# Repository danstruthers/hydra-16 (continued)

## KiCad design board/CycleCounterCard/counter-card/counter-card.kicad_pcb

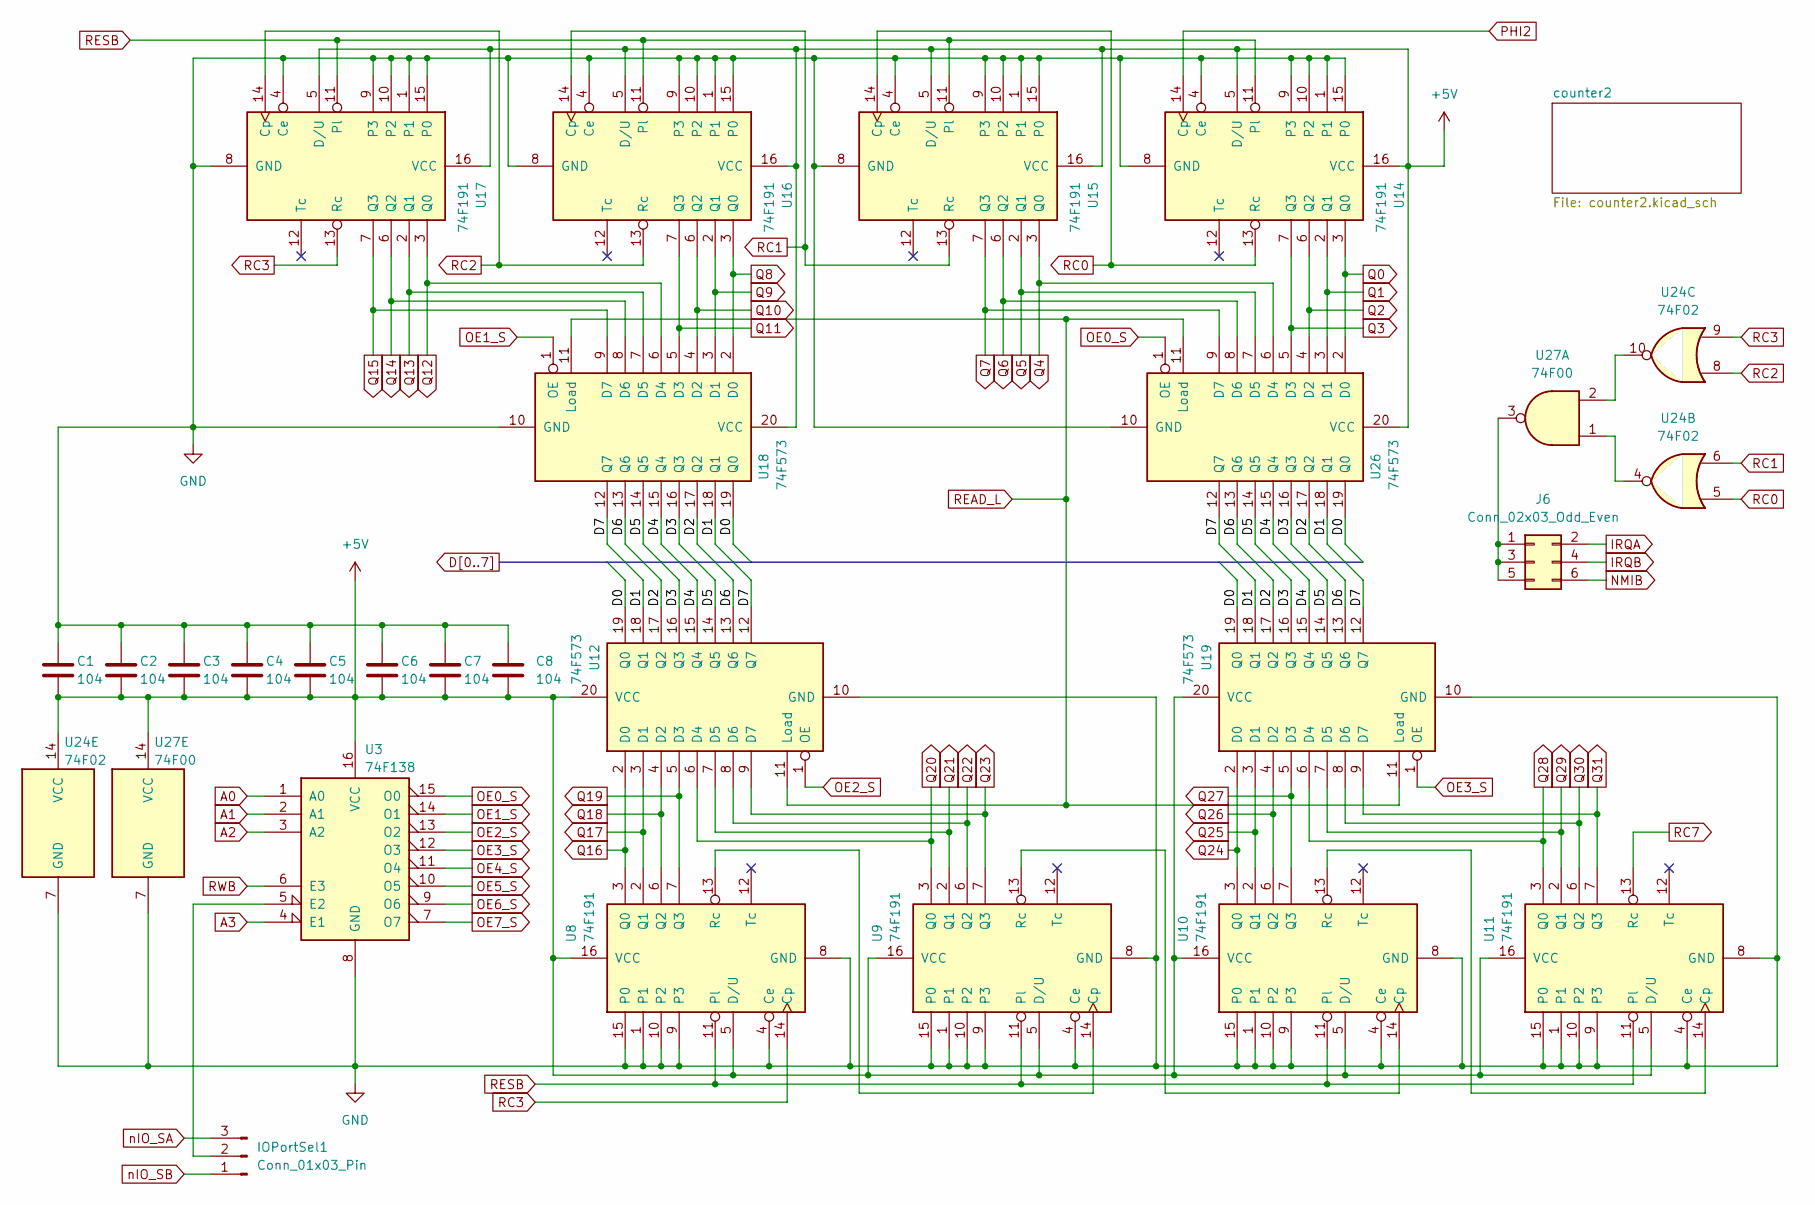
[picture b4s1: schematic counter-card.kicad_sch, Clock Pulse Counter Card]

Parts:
C1, C2, C3, C4, C5, C6, C7, C8: 104; C_Disc_D5.0mm_W2.5mm_P5.00mm
IOPortSel1: Conn_01x03_Pin; PinHeader_1x03_P2.54mm_Vertical
J6: Conn_02x03_Odd_Even; PinHeader_2x03_P2.54mm_Vertical
U3: 74F138; DIP-16_W7.62mm_Socket_LongPads
U8, U9, U10, U11, U14, U15, U16, U17: 74F191; DIP-16_W7.62mm_Socket_LongPads
U12, U18, U19, U26: 74F573; DIP-20_W7.62mm_Socket_LongPads
U24: 74F02; DIP-14_W7.62mm_Socket_LongPads
U27: 74F00; DIP-14_W7.62mm_Socket_LongPads

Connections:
+5V: C1.2, C2.2, C3.2, C4.2, C5.2, C6.2, C7.2, C8.2, U3.16 (VCC), U8.5 (D/U), U8.16 (VCC), U9.5 (D/U), U9.16 (VCC), U10.5 (D/U), U10.16 (VCC), U11.5 (D/U), U11.16 (VCC), U12.20 (VCC), U14.5 (D/U), U14.16 (VCC), U15.5 (D/U), U15.16 (VCC), U16.5 (D/U), U16.16 (VCC), U17.5 (D/U), U17.16 (VCC), U18.20 (VCC), U19.20 (VCC), U24.14 (VCC), U26.20 (VCC), U27.14 (VCC); also elsewhere on the board
A0: U3.1 (A0); also elsewhere on the board
A1: U3.2 (A1); also elsewhere on the board
A2: U3.3 (A2); also elsewhere on the board
A3: U3.4 (E1); also elsewhere on the board
D0: U12.19 (Q0), U18.19 (Q0), U19.19 (Q0), U26.19 (Q0); also elsewhere on the board
D1: U12.18 (Q1), U18.18 (Q1), U19.18 (Q1), U26.18 (Q1); also elsewhere on the board
D2: U12.17 (Q2), U18.17 (Q2), U19.17 (Q2), U26.17 (Q2); also elsewhere on the board
D3: U12.16 (Q3), U18.16 (Q3), U19.16 (Q3), U26.16 (Q3); also elsewhere on the board
D4: U12.15 (Q4), U18.15 (Q4), U19.15 (Q4), U26.15 (Q4); also elsewhere on the board
D5: U12.14 (Q5), U18.14 (Q5), U19.14 (Q5), U26.14 (Q5); also elsewhere on the board
D6: U12.13 (Q6), U18.13 (Q6), U19.13 (Q6), U26.13 (Q6); also elsewhere on the board
D7: U12.12 (Q7), U18.12 (Q7), U19.12 (Q7), U26.12 (Q7); also elsewhere on the board
GND: C1.1, C2.1, C3.1, C4.1, C5.1, C6.1, C7.1, C8.1, U3.8 (GND), U8.1, U8.4 (Ce), U8.8 (GND), U8.9 (P3), U8.10 (P2), U8.15 (P0), U9.1, U9.4 (Ce), U9.8 (GND), U9.9 (P3), U9.10 (P2), U9.15 (P0), U10.1, U10.4 (Ce), U10.8 (GND), U10.9 (P3), U10.10 (P2), U10.15 (P0), U11.1, U11.4 (Ce), U11.8 (GND), U11.9 (P3), U11.10 (P2), U11.15 (P0), U12.10 (GND), U14.1, U14.4 (Ce), U14.8 (GND), U14.9 (P3), U14.10 (P2), U14.15 (P0), U15.1, U15.4 (Ce), U15.8 (GND), U15.9 (P3), U15.10 (P2), U15.15 (P0), U16.1, U16.4 (Ce), U16.8 (GND), U16.9 (P3), U16.10 (P2), U16.15 (P0), U17.1, U17.4 (Ce), U17.8 (GND), U17.9 (P3), U17.10 (P2), U17.15 (P0), U18.10 (GND), U19.10 (GND), U24.7 (GND), U26.10 (GND), U27.7 (GND); also elsewhere on the board
IRQA: J6.2; also elsewhere on the board
IRQB: J6.4; also elsewhere on the board
NMIB: J6.6; also elsewhere on the board
unnamed: IOPortSel1.2, U3.5 (E2)
unnamed: J6.1, J6.3, J6.5, U27.3
unnamed: U8.13 (Rc), U9.14 (Cp)
unnamed: U9.13 (Rc), U10.14 (Cp)
unnamed: U10.13 (Rc), U11.14 (Cp)
unnamed: U24.4, U27.1
unnamed: U24.10, U27.2
OE0_S: U3.15 (O0), U26.1 (OE); also elsewhere on the board
OE1_S: U3.14 (O1), U18.1 (OE)
OE2_S: U3.13 (O2), U12.1 (OE)
OE3_S: U3.12 (O3), U19.1 (OE)
OE4_S: U3.11 (O4); also elsewhere on the board
OE5_S: U3.10 (O5); also elsewhere on the board
OE6_S: U3.9 (O6); also elsewhere on the board
OE7_S: U3.7 (O7); also elsewhere on the board
PHI2: U14.14 (Cp); also elsewhere on the board
Q0: U14.3 (Q0), U26.2 (D0); also elsewhere on the board
Q1: U14.2 (Q1), U26.3 (D1); also elsewhere on the board
Q2: U14.6 (Q2), U26.4 (D2); also elsewhere on the board
Q3: U14.7 (Q3), U26.5 (D3); also elsewhere on the board
Q4: U15.3 (Q0), U26.6 (D4); also elsewhere on the board
Q5: U15.2 (Q1), U26.7 (D5); also elsewhere on the board
Q6: U15.6 (Q2), U26.8 (D6); also elsewhere on the board
Q7: U15.7 (Q3), U26.9 (D7); also elsewhere on the board
Q8: U16.3 (Q0), U18.2 (D0); also elsewhere on the board
Q9: U16.2 (Q1), U18.3 (D1); also elsewhere on the board
Q10: U16.6 (Q2), U18.4 (D2); also elsewhere on the board
Q11: U16.7 (Q3), U18.5 (D3); also elsewhere on the board
Q12: U17.3 (Q0), U18.6 (D4); also elsewhere on the board
Q13: U17.2 (Q1), U18.7 (D5); also elsewhere on the board
Q14: U17.6 (Q2), U18.8 (D6); also elsewhere on the board
Q15: U17.7 (Q3), U18.9 (D7); also elsewhere on the board
Q16: U8.3 (Q0), U12.2 (D0); also elsewhere on the board
Q17: U8.2 (Q1), U12.3 (D1); also elsewhere on the board
Q18: U8.6 (Q2), U12.4 (D2); also elsewhere on the board
Q19: U8.7 (Q3), U12.5 (D3); also elsewhere on the board
Q20: U9.3 (Q0), U12.6 (D4); also elsewhere on the board
Q21: U9.2 (Q1), U12.7 (D5); also elsewhere on the board
Q22: U9.6 (Q2), U12.8 (D6); also elsewhere on the board
Q23: U9.7 (Q3), U12.9 (D7); also elsewhere on the board
Q24: U10.3 (Q0), U19.2 (D0); also elsewhere on the board
Q25: U10.2 (Q1), U19.3 (D1); also elsewhere on the board
Q26: U10.6 (Q2), U19.4 (D2); also elsewhere on the board
Q27: U10.7 (Q3), U19.5 (D3); also elsewhere on the board
Q28: U11.3 (Q0), U19.6 (D4); also elsewhere on the board
Q29: U11.2 (Q1), U19.7 (D5); also elsewhere on the board
Q30: U11.6 (Q2), U19.8 (D6); also elsewhere on the board
Q31: U11.7 (Q3), U19.9 (D7); also elsewhere on the board
RC0: U14.13 (Rc), U15.14 (Cp), U24.5
RC1: U15.13 (Rc), U16.14 (Cp), U24.6
RC2: U16.13 (Rc), U17.14 (Cp), U24.8
RC3: U8.14 (Cp), U17.13 (Rc), U24.9
RC7: U11.13 (Rc); also elsewhere on the board
READ_L: U12.11 (Load), U18.11 (Load), U19.11 (Load), U26.11 (Load); also elsewhere on the board
RESB: U8.11 (Pl), U9.11 (Pl), U10.11 (Pl), U11.11 (Pl), U14.11 (Pl), U15.11 (Pl), U16.11 (Pl), U17.11 (Pl); also elsewhere on the board
RWB: U3.6 (E3); also elsewhere on the board
nIO_SA: IOPortSel1.3; also elsewhere on the board
nIO_SB: IOPortSel1.1; also elsewhere on the board

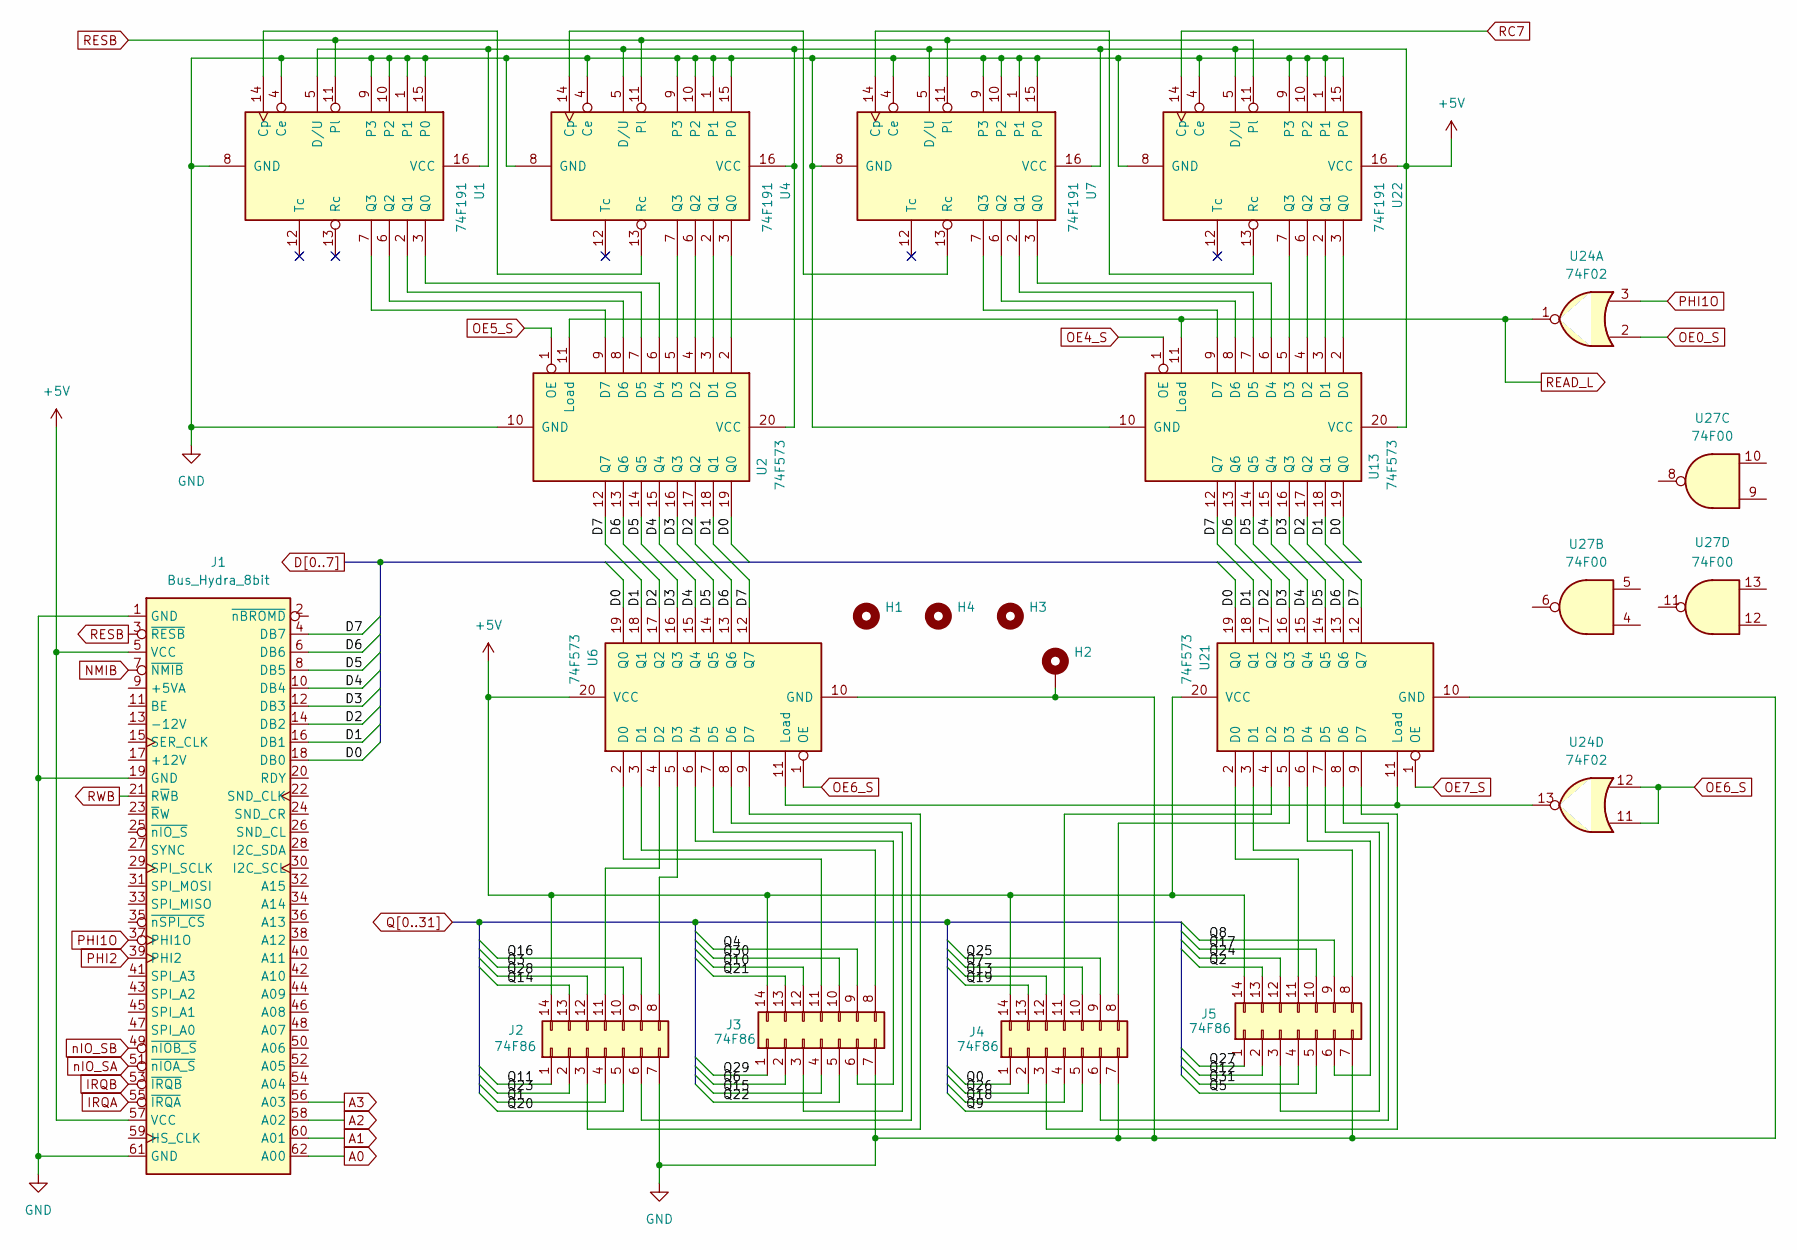
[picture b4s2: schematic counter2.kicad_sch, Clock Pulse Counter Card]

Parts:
H1, H3: MountingHole_3.2mm_M3
H2: MountingHole_Pad; MountingHole_3.2mm_M3_ISO7380_Pad_TopBottom
H4: MountingHole_3.2mm_M3_ISO7380_Pad_TopBottom; MountingHole_3.2mm_M3
J1: Bus_Hydra_8bit; BUS_Hydra_8Bit
J2, J3, J4, J5: 74F86; DIP-14_W7.62mm_Socket_LongPads
U1, U4, U7, U22: 74F191; DIP-16_W7.62mm_Socket_LongPads
U2, U6, U13, U21: 74F573; DIP-20_W7.62mm_Socket_LongPads
U24: 74F02; DIP-14_W7.62mm_Socket_LongPads
U27: 74F00; DIP-14_W7.62mm_Socket_LongPads

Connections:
+5V: J1.5 (VCC), J1.57 (VCC), J2.14, J3.14, J4.14, J5.14, U1.5 (D/U), U1.16 (VCC), U2.20 (VCC), U4.5 (D/U), U4.16 (VCC), U6.20 (VCC), U7.5 (D/U), U7.16 (VCC), U13.20 (VCC), U21.20 (VCC), U22.5 (D/U), U22.16 (VCC); also elsewhere on the board
A0: J1.62 (A00); also elsewhere on the board
A1: J1.60 (A01); also elsewhere on the board
A2: J1.58 (A02); also elsewhere on the board
A3: J1.56 (A03); also elsewhere on the board
D0: J1.18 (DB0), U2.19 (Q0), U6.19 (Q0), U13.19 (Q0), U21.19 (Q0); also elsewhere on the board
D1: J1.16 (DB1), U2.18 (Q1), U6.18 (Q1), U13.18 (Q1), U21.18 (Q1); also elsewhere on the board
D2: J1.14 (DB2), U2.17 (Q2), U6.17 (Q2), U13.17 (Q2), U21.17 (Q2); also elsewhere on the board
D3: J1.12 (DB3), U2.16 (Q3), U6.16 (Q3), U13.16 (Q3), U21.16 (Q3); also elsewhere on the board
D4: J1.10 (DB4), U2.15 (Q4), U6.15 (Q4), U13.15 (Q4), U21.15 (Q4); also elsewhere on the board
D5: J1.8 (DB5), U2.14 (Q5), U6.14 (Q5), U13.14 (Q5), U21.14 (Q5); also elsewhere on the board
D6: J1.6 (DB6), U2.13 (Q6), U6.13 (Q6), U13.13 (Q6), U21.13 (Q6); also elsewhere on the board
D7: J1.4 (DB7), U2.12 (Q7), U6.12 (Q7), U13.12 (Q7), U21.12 (Q7); also elsewhere on the board
GND: H2.1, J1.1 (GND), J1.19 (GND), J1.61 (GND), J2.7, J3.7, J4.7, J5.7, U1.1, U1.4 (Ce), U1.8 (GND), U1.9 (P3), U1.10 (P2), U1.15 (P0), U2.10 (GND), U4.1, U4.4 (Ce), U4.8 (GND), U4.9 (P3), U4.10 (P2), U4.15 (P0), U6.10 (GND), U7.1, U7.4 (Ce), U7.8 (GND), U7.9 (P3), U7.10 (P2), U7.15 (P0), U13.10 (GND), U21.10 (GND), U22.1, U22.4 (Ce), U22.8 (GND), U22.9 (P3), U22.10 (P2), U22.15 (P0); also elsewhere on the board
IRQA: J1.55 (~IRQA); also elsewhere on the board
IRQB: J1.53 (~IRQB); also elsewhere on the board
NMIB: J1.7 (~NMIB); also elsewhere on the board
unnamed: J2.3, U6.9 (D7)
unnamed: J2.6, U6.8 (D6)
unnamed: J2.8, U6.5 (D3)
unnamed: J2.11, U6.4 (D2)
unnamed: J3.3, U6.7 (D5)
unnamed: J3.6, U6.6 (D4)
unnamed: J3.8, U6.3 (D1)
unnamed: J3.11, U6.2 (D0)
unnamed: J4.3, U21.9 (D7)
unnamed: J4.6, U21.8 (D6)
unnamed: J4.8, U21.5 (D3)
unnamed: J4.11, U21.4 (D2)
unnamed: J5.3, U21.7 (D5)
unnamed: J5.6, U21.6 (D4)
unnamed: J5.8, U21.3 (D1)
unnamed: J5.11, U21.2 (D0)
unnamed: U1.14 (Cp), U4.13 (Rc)
unnamed: U1.3 (Q0), U2.6 (D4)
unnamed: U1.2 (Q1), U2.7 (D5)
unnamed: U1.6 (Q2), U2.8 (D6)
unnamed: U1.7 (Q3), U2.9 (D7)
unnamed: U2.2 (D0), U4.3 (Q0)
unnamed: U2.3 (D1), U4.2 (Q1)
unnamed: U2.4 (D2), U4.6 (Q2)
unnamed: U2.5 (D3), U4.7 (Q3)
unnamed: U4.14 (Cp), U7.13 (Rc)
unnamed: U13.2 (D0), U22.3 (Q0)
unnamed: U13.3 (D1), U22.2 (Q1)
unnamed: U13.4 (D2), U22.6 (Q2)
unnamed: U13.5 (D3), U22.7 (Q3)
unnamed: U7.3 (Q0), U13.6 (D4)
unnamed: U7.2 (Q1), U13.7 (D5)
unnamed: U7.6 (Q2), U13.8 (D6)
unnamed: U7.7 (Q3), U13.9 (D7)
unnamed: U6.11 (Load), U21.11 (Load), U24.13
unnamed: U7.14 (Cp), U22.13 (Rc)
OE0_S: U24.2; also elsewhere on the board
OE4_S: U13.1 (OE); also elsewhere on the board
OE5_S: U2.1 (OE); also elsewhere on the board
OE6_S: U6.1 (OE), U24.11, U24.12; also elsewhere on the board
OE7_S: U21.1 (OE); also elsewhere on the board
PHI1O: J1.37 (PHI1O), U24.3
PHI2: J1.39 (PHI2); also elsewhere on the board
Q0: J4.1; also elsewhere on the board
Q1: J2.4; also elsewhere on the board
Q2: J5.13; also elsewhere on the board
Q3: J2.10; also elsewhere on the board
Q4: J3.9; also elsewhere on the board
Q5: J5.5; also elsewhere on the board
Q6: J3.2; also elsewhere on the board
Q7: J4.10; also elsewhere on the board
Q8: J5.9; also elsewhere on the board
Q9: J4.5; also elsewhere on the board
Q10: J3.12; also elsewhere on the board
Q11: J2.1; also elsewhere on the board
Q12: J5.2; also elsewhere on the board
Q13: J4.12; also elsewhere on the board
Q14: J2.13; also elsewhere on the board
Q15: J3.4; also elsewhere on the board
Q16: J2.9; also elsewhere on the board
Q17: J5.10; also elsewhere on the board
Q18: J4.4; also elsewhere on the board
Q19: J4.13; also elsewhere on the board
Q20: J2.5; also elsewhere on the board
Q21: J3.13; also elsewhere on the board
Q22: J3.5; also elsewhere on the board
Q23: J2.2; also elsewhere on the board
Q24: J5.12; also elsewhere on the board
Q25: J4.9; also elsewhere on the board
Q26: J4.2; also elsewhere on the board
Q27: J5.1; also elsewhere on the board
Q28: J2.12; also elsewhere on the board
Q29: J3.1; also elsewhere on the board
Q30: J3.10; also elsewhere on the board
Q31: J5.4; also elsewhere on the board
RC7: U22.14 (Cp); also elsewhere on the board
READ_L: U2.11 (Load), U13.11 (Load), U24.1; also elsewhere on the board
RESB: J1.3 (~RESB), U1.11 (Pl), U4.11 (Pl), U7.11 (Pl), U22.11 (Pl); also elsewhere on the board
RWB: J1.21 (R~WB); also elsewhere on the board
nIO_SA: J1.51 (~nIOA_S); also elsewhere on the board
nIO_SB: J1.49 (~nIOB_S); also elsewhere on the board

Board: 4 copper layers, 42 parts (0 on the bottom side), 112 nets, no tracks yet.

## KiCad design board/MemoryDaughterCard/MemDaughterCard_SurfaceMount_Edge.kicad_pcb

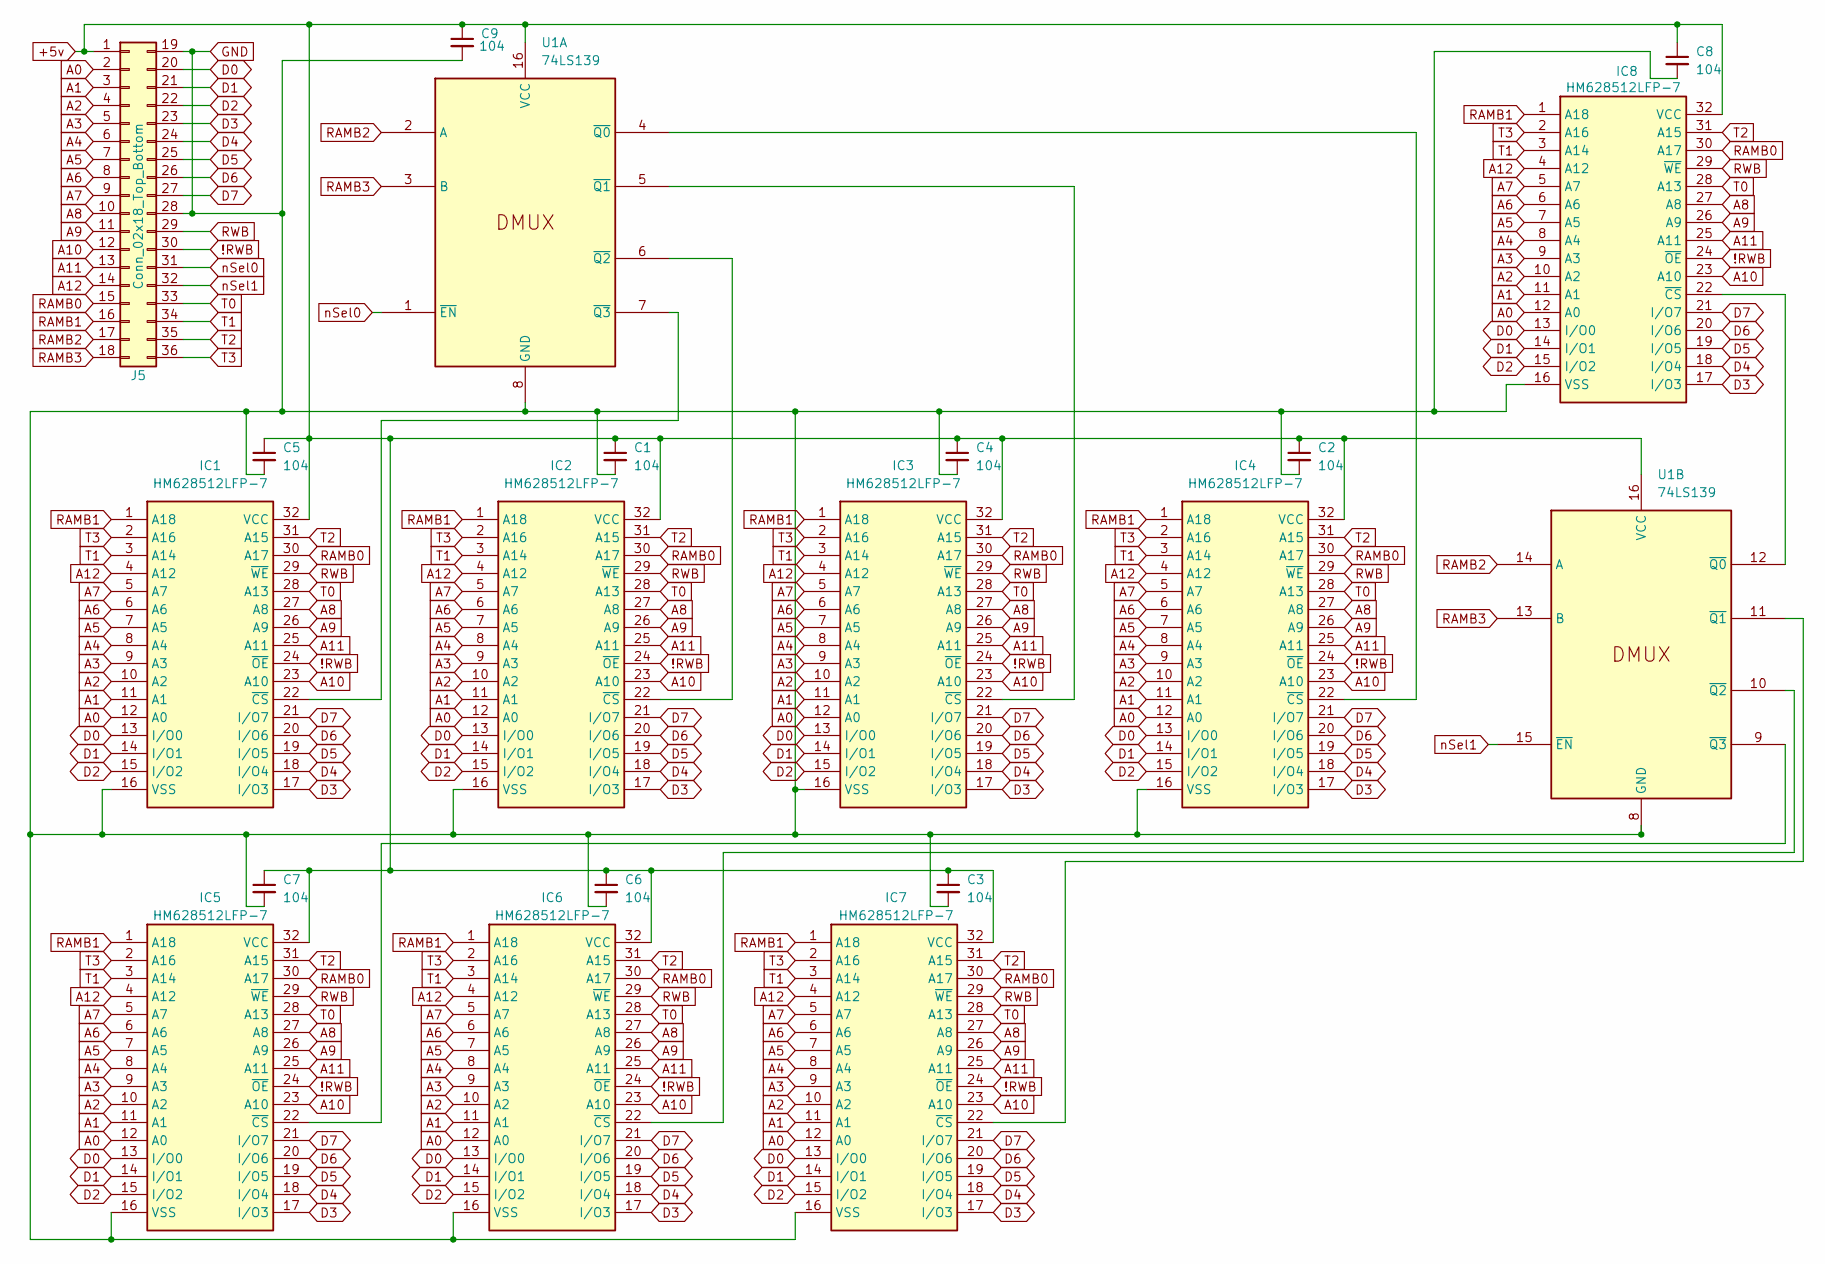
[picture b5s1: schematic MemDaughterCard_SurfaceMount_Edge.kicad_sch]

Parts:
C1, C2, C3, C4, C5, C6, C7, C8, C9: 104; C_Disc_D5.0mm_W2.5mm_P5.00mm
IC1, IC2, IC3, IC4, IC5, IC6, IC7, IC8: HM628512LFP-7; SOIC127P1414X300-32N; Manufacturer_Part_Number HM628512LFP-7
J5: Conn_02x18_Top_Bottom; Bus_Hydra_Mem
U1: 74LS139; DIP-16_W7.62mm

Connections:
!RWB: IC1.24 (~OE), IC2.24 (~OE), IC3.24 (~OE), IC4.24 (~OE), IC5.24 (~OE), IC6.24 (~OE), IC7.24 (~OE), IC8.24 (~OE), J5.30
+5v: C1.1, C2.1, C3.1, C4.1, C5.1, C6.1, C7.1, C8.1, C9.1, IC1.32 (VCC), IC2.32 (VCC), IC3.32 (VCC), IC4.32 (VCC), IC5.32 (VCC), IC6.32 (VCC), IC7.32 (VCC), IC8.32 (VCC), J5.1, U1.16 (VCC)
A0: IC1.12 (A0), IC2.12 (A0), IC3.12 (A0), IC4.12 (A0), IC5.12 (A0), IC6.12 (A0), IC7.12 (A0), IC8.12 (A0), J5.2
A1: IC1.11 (A1), IC2.11 (A1), IC3.11 (A1), IC4.11 (A1), IC5.11 (A1), IC6.11 (A1), IC7.11 (A1), IC8.11 (A1), J5.3
A2: IC1.10 (A2), IC2.10 (A2), IC3.10 (A2), IC4.10 (A2), IC5.10 (A2), IC6.10 (A2), IC7.10 (A2), IC8.10 (A2), J5.4
A3: IC1.9 (A3), IC2.9 (A3), IC3.9 (A3), IC4.9 (A3), IC5.9 (A3), IC6.9 (A3), IC7.9 (A3), IC8.9 (A3), J5.5
A4: IC1.8 (A4), IC2.8 (A4), IC3.8 (A4), IC4.8 (A4), IC5.8 (A4), IC6.8 (A4), IC7.8 (A4), IC8.8 (A4), J5.6
A5: IC1.7 (A5), IC2.7 (A5), IC3.7 (A5), IC4.7 (A5), IC5.7 (A5), IC6.7 (A5), IC7.7 (A5), IC8.7 (A5), J5.7
A6: IC1.6 (A6), IC2.6 (A6), IC3.6 (A6), IC4.6 (A6), IC5.6 (A6), IC6.6 (A6), IC7.6 (A6), IC8.6 (A6), J5.8
A7: IC1.5 (A7), IC2.5 (A7), IC3.5 (A7), IC4.5 (A7), IC5.5 (A7), IC6.5 (A7), IC7.5 (A7), IC8.5 (A7), J5.9
A8: IC1.27 (A8), IC2.27 (A8), IC3.27 (A8), IC4.27 (A8), IC5.27 (A8), IC6.27 (A8), IC7.27 (A8), IC8.27 (A8), J5.10
A9: IC1.26 (A9), IC2.26 (A9), IC3.26 (A9), IC4.26 (A9), IC5.26 (A9), IC6.26 (A9), IC7.26 (A9), IC8.26 (A9), J5.11
A10: IC1.23 (A10), IC2.23 (A10), IC3.23 (A10), IC4.23 (A10), IC5.23 (A10), IC6.23 (A10), IC7.23 (A10), IC8.23 (A10), J5.12
A11: IC1.25 (A11), IC2.25 (A11), IC3.25 (A11), IC4.25 (A11), IC5.25 (A11), IC6.25 (A11), IC7.25 (A11), IC8.25 (A11), J5.13
A12: IC1.4 (A12), IC2.4 (A12), IC3.4 (A12), IC4.4 (A12), IC5.4 (A12), IC6.4 (A12), IC7.4 (A12), IC8.4 (A12), J5.14
D0: IC1.13 (I/O0), IC2.13 (I/O0), IC3.13 (I/O0), IC4.13 (I/O0), IC5.13 (I/O0), IC6.13 (I/O0), IC7.13 (I/O0), IC8.13 (I/O0), J5.20
D1: IC1.14 (I/O1), IC2.14 (I/O1), IC3.14 (I/O1), IC4.14 (I/O1), IC5.14 (I/O1), IC6.14 (I/O1), IC7.14 (I/O1), IC8.14 (I/O1), J5.21
D2: IC1.15 (I/O2), IC2.15 (I/O2), IC3.15 (I/O2), IC4.15 (I/O2), IC5.15 (I/O2), IC6.15 (I/O2), IC7.15 (I/O2), IC8.15 (I/O2), J5.22
D3: IC1.17 (I/O3), IC2.17 (I/O3), IC3.17 (I/O3), IC4.17 (I/O3), IC5.17 (I/O3), IC6.17 (I/O3), IC7.17 (I/O3), IC8.17 (I/O3), J5.23
D4: IC1.18 (I/O4), IC2.18 (I/O4), IC3.18 (I/O4), IC4.18 (I/O4), IC5.18 (I/O4), IC6.18 (I/O4), IC7.18 (I/O4), IC8.18 (I/O4), J5.24
D5: IC1.19 (I/O5), IC2.19 (I/O5), IC3.19 (I/O5), IC4.19 (I/O5), IC5.19 (I/O5), IC6.19 (I/O5), IC7.19 (I/O5), IC8.19 (I/O5), J5.25
D6: IC1.20 (I/O6), IC2.20 (I/O6), IC3.20 (I/O6), IC4.20 (I/O6), IC5.20 (I/O6), IC6.20 (I/O6), IC7.20 (I/O6), IC8.20 (I/O6), J5.26
D7: IC1.21 (I/O7), IC2.21 (I/O7), IC3.21 (I/O7), IC4.21 (I/O7), IC5.21 (I/O7), IC6.21 (I/O7), IC7.21 (I/O7), IC8.21 (I/O7), J5.27
GND: C1.2, C2.2, C3.2, C4.2, C5.2, C6.2, C7.2, C8.2, C9.2, IC1.16 (VSS), IC2.16 (VSS), IC3.16 (VSS), IC4.16 (VSS), IC5.16 (VSS), IC6.16 (VSS), IC7.16 (VSS), IC8.16 (VSS), J5.19, J5.28, U1.8 (GND)
unnamed: IC1.22 (~CS), U1.7 (~Q3)
unnamed: IC2.22 (~CS), U1.6 (~Q2)
unnamed: IC3.22 (~CS), U1.5 (~Q1)
unnamed: IC4.22 (~CS), U1.4 (~Q0)
unnamed: IC5.22 (~CS), U1.9 (~Q3)
unnamed: IC6.22 (~CS), U1.10 (~Q2)
unnamed: IC7.22 (~CS), U1.11 (~Q1)
unnamed: IC8.22 (~CS), U1.12 (~Q0)
RAMB0: IC1.30 (A17), IC2.30 (A17), IC3.30 (A17), IC4.30 (A17), IC5.30 (A17), IC6.30 (A17), IC7.30 (A17), IC8.30 (A17), J5.15
RAMB1: IC1.1 (A18), IC2.1 (A18), IC3.1 (A18), IC4.1 (A18), IC5.1 (A18), IC6.1 (A18), IC7.1 (A18), IC8.1 (A18), J5.16
RAMB2: J5.17, U1.2 (A), U1.14 (A)
RAMB3: J5.18, U1.3 (B), U1.13 (B)
RWB: IC1.29 (~WE), IC2.29 (~WE), IC3.29 (~WE), IC4.29 (~WE), IC5.29 (~WE), IC6.29 (~WE), IC7.29 (~WE), IC8.29 (~WE), J5.29
T0: IC1.28 (A13), IC2.28 (A13), IC3.28 (A13), IC4.28 (A13), IC5.28 (A13), IC6.28 (A13), IC7.28 (A13), IC8.28 (A13), J5.33
T1: IC1.3 (A14), IC2.3 (A14), IC3.3 (A14), IC4.3 (A14), IC5.3 (A14), IC6.3 (A14), IC7.3 (A14), IC8.3 (A14), J5.34
T2: IC1.31 (A15), IC2.31 (A15), IC3.31 (A15), IC4.31 (A15), IC5.31 (A15), IC6.31 (A15), IC7.31 (A15), IC8.31 (A15), J5.35
T3: IC1.2 (A16), IC2.2 (A16), IC3.2 (A16), IC4.2 (A16), IC5.2 (A16), IC6.2 (A16), IC7.2 (A16), IC8.2 (A16), J5.36
nSel0: J5.31, U1.1 (~EN)
nSel1: J5.32, U1.15 (~EN)

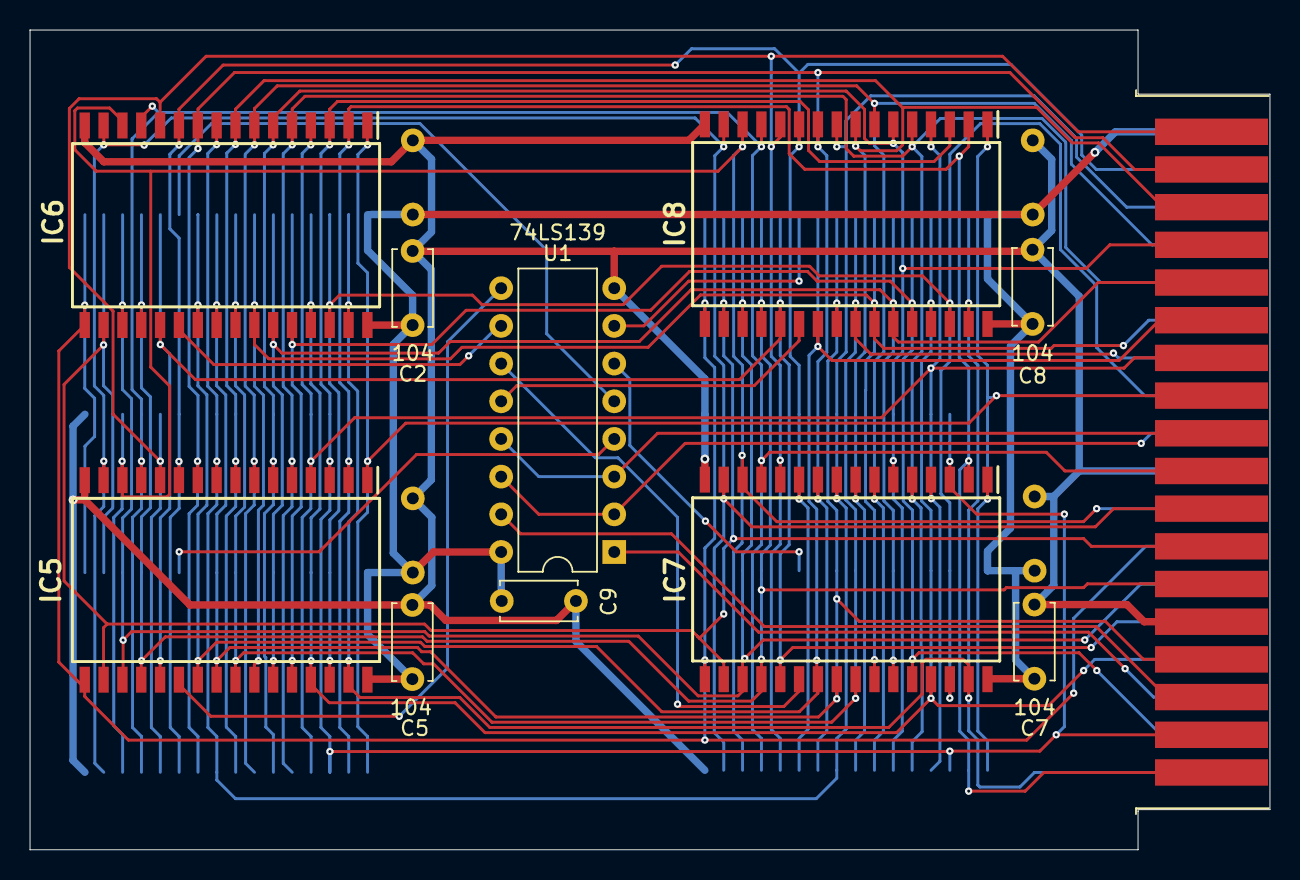
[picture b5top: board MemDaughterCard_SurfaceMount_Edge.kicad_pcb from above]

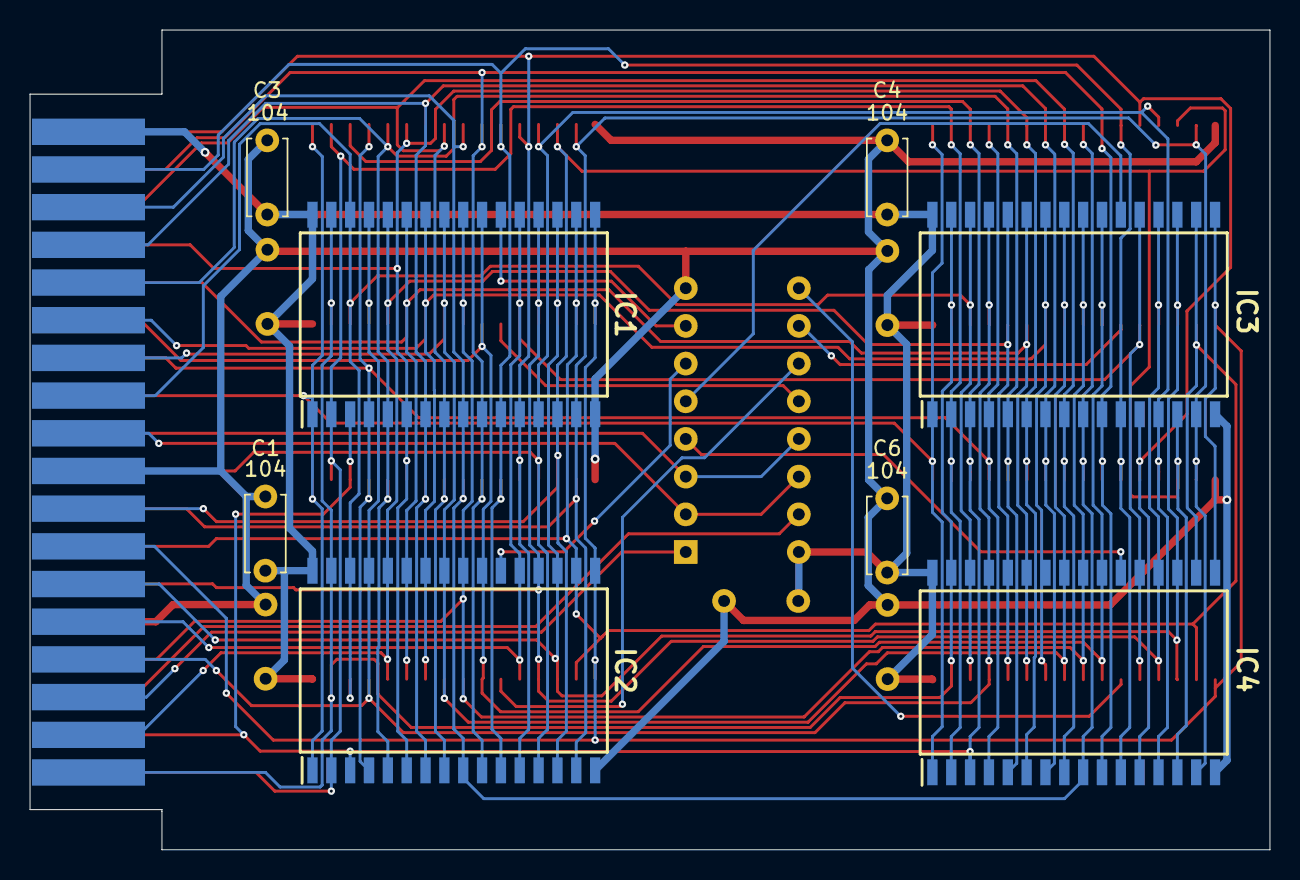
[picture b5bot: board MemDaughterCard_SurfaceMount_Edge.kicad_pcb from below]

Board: 2 copper layers, 83.6 x 55.2 mm, 19 parts (8 on the bottom side), 43 nets.
